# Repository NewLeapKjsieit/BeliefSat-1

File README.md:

# BeliefSat-1

BeliefSat-1 is a 2p-PocketQube standard student nano-satellite being developed by the undergraduate students of [**_K.J.Somaiya Institute of Engineering and Information Technology, Sion, Mumbai_** .](https://kjsieit.somaiya.edu/en) The satellite itself is a sub-part of team's proposal under [PS4-Orbital platform program](https://www.isro.gov.in/update/15-jun-2019/announcement-of-opportunity-ao-orbital-platform) of ISRO, wherein, team aims to demonstrate indegenously developed technologies for PocketQube standard nano-satellites. As a part of this demonstration, **BeliefSat** will be launched out of **SomaiyaPod** which is a Pocketqube standard deployer being indegenously developed at the institute. The unique construction technique, combination of COTS components for communication, on-board computer and power sub-systems , together constitute of **SomaiyaPQBus**, around which the satellite is being made, is also one of the technologies that the team wants to demonstrate and open-source to enable use by future missions.

## So what will BeliefSat do in space and what results it will give?

1. If it is successfully deployed out of the SomaiyaPod and completes startup procedure (it will be dead inside the Pod and will only get power after it is out of pod)and then sends a beacon; reliability of both deployer and the design of the satellite will be confirmed.
2. Every 1 minute, it will send a telemetry packet, which will have values from different COTS sensors. The team aims to project the activity of telemetry reception as a way of involving more students in to Software Defined Radio and RF in general.
3. It will have a functionality as of a amateur-radio digipeater. Which means if you hold a proper Amateur radio license then you can send a text message to the satellite and the satellite will repeat it (after delay of upto 10 seconds depending on other important processes running on-board). Making it a utility for Amateur radio community.
4. Not only it can digipeat a message it also has the functionality to repeat voice. For using this functionality you need a UHF transmitter and you can send a voice message to the satellite and the satellite will repeate it (after some delay depending on other important processes running on-board). It also will be a big utility for Amateur radio community.
5. If the satellite is able to operate for more than 3 months while responding to the commands and sending the health data at proper intervals, it will prove the reliablity of the unique design and set of COTS hardware used. Thus future mission could use flight proven hardwares for communication and power generation.

## What is it made of ?, What does it look like ?, What are its dimenssions and mass?

BeliefSat's structure is made by joining plates/PCBs(made out of FR4 material). This is a very novel approach in designing the structure of a satellite. Generally, satellites are made from Aluminium or its alloys, but using our novel approach we were able to design a very sturdy but cost effective sateliite. Although this technique is generally limited to nano-satellites. The PCBs that make the structure of our satellite have the solar panels and other components embedded in itself, so the complexity of assembly is minimized.

This is a concept render of our BeliefSat:

The dimension of the BeliefSat is in accordance with the PocketQube Standards. This standard includes a base plate on which the satellite is mounted and then it slides out of
the satellite deployer via rails. As per the standards, our BeliefSat is 2P ie, Base plate is 58mm x 128mm x 1.6mm (WxLxH), whereas the satellite is 58mm x 128mm x 50mm (WxLxH).
The estimated mass of BeliefSat is around 450 grams. The dimensions of our deployer (SomaiyaPod) are 145mm x 200mm x 95mm (WxLxH).

## How is it powered?

The satellite is powered by AltaDevices Single Juntion cells ([which unfortunately are out of buisness as of date of writing](https://pv-magazine-usa.com/2019/12/31/shutdown-continues-at-hanergy-owned-alta-devices-high-efficiency-pv-pioneer/)). Each of these cell produce 0.25W power when illumniated at intensity of 1000W/m^2. There are 4 such cells on long sides and 2 on shorter sides. So when illuminated, satellite may produce 0.5W watt/1watt/>1W depending on the orientation. The power remaining after being used is then stored in 2 parallely connected [2600mah Samsung 18650 batteries](https://robokits.co.in/batteries-chargers/samsung-premium-li-ion-battery/3.7v-samsung-li-ion-batteries/samsung-icr-18650-26j-2600mah-li-ion-cell-original?gclid=CjwKCAjwltH3BRB6EiwAhj0IUHaLyAB-D4SHw_PhNjM4cJyQy68a7cGyKCsCMS-I6JLJSGFChlp92BoC6-4QAvD_BwE). [SPV1040](https://www.st.com/en/power-management/spv1040.html) is used on every panel for maximum power point tracking and giving regulated voltage from the solar cells. The choice of SPV1040 was made based on flight history in [FossaSat-1](https://github.com/FOSSASystems/FOSSASAT-1). Now that AltaDevices cells won't be available in market, team will also be making one prototype with [SM141K06L by IXYS](https://www.digikey.com/product-detail/en/ixys/SM141K06L/SM141K06L-ND/9990462) and will be publishing test results for it too. 

## How does it communicate?

**_Transciever Specs_**
    **VHF**
-   **Name :** [DRA818V](http://www.dorji.com/products.php?Keyword=dra818v)
-   **Frequency Range :** 134~174 Mhz
-   **Channel Space :** 12.5/25 KHz
-   **TX Current :** 450/750 mA
-   **Temperature :** -20°C ~ +70°C
-   **Output Power :** +27/30 dbm
-   **Reciever Sensitivity :** -122 dbm (As per datasheet, observed sensititvity yet to be calculated)

    **UHF**
-   **Name :** [DRA818U](http://www.dorji.com/products.php?Keyword=dra818u)
-   **Frequency Range :** 400~470 Mhz
-   **Channel Space :** 25 KHz
-   **TX Current :** 450/750 mA
-   **Temperature :** -20°C ~ +70°C
-   **Output Power :** +27/30 dbm
-   **Reciever Sensitivity :** -122 dbm (As per datasheet, observed sensititvity yet to be calculated)
    _(UHF will only be used for voice repeater uplink)_
**_Antenna_**

Dipole made from measuring tape, which is in folded state during launch. Once in orbit, fishing cord which holds the antenna in folded position, is burnt by heating a resistor around which it is tied.

**_Link Budget_**

-   **Orbit Height :** 600 Km (proposed, may vary as per allocation by launch provider)
-   **Slant Range at 25 degree elevation :** 1213.4 Km (approximately)
-   **Free Space Path Loss at this distance for 145.825 MHz frequency :** 137.4 dbm
-   **Free Space Path Loss at this distance for 435.6 MHz frequency :** 146.9 dbm
-   **Received power neglecting mismatch,connector,atmospheric, pointing and polarization losses and receiving and transmitting antenna gains :** -118.2/-121.2 (op= 30/27dbm)
-   **Note :** A good directional antenna at receving groundstation (e.g. a 6 element yagi, plans for which will be released soon) can ensure the above mentioned losses are made up for and the signals can be received at even lower angles. However, to ensure best performance, circular polarized antennas copuled with a good LNA (e.g. [LNA4ALL](http://lna4all.blogspot.com/)) mounted over a Azimuth-Elevation antenna rotator (e.g. [Satnogs rotator](https://wiki.satnogs.org/SatNOGS_Rotator_v3)/[Sarcnet Rotator](https://www.sarcnet.org/rotator-mk2.html#RotatorMk2a)/[Yaesu G5500](https://www.yaesu.com/indexVS.cfm?cmd=DisplayProducts&ProdCatID=104&encProdID=79A89CEC477AA3B819EE02831F3FD5B8)/[WRAPS portable antenna rotator](https://ukamsat.files.wordpress.com/2013/12/wraps-mark-spencer-wa8sme-qst-jan-2014-copyright-arrl.pdf)) is recommended.

**_Data Rates in bps_**

-   **Telemetry Downlink :** 1200
-   **Digipeater Downlink :** 1200
-   **Command Uplink :** 1200
-   **Digipeater Uplink :** 1200

**_How the satellite complies with the requirment of turning off the transmitters when required ?_**
All the uplinks and downlinks occur on same frequency. Reciever is disabled while transmitting, to avoid interrupts to controller during the transmission, however, these transmissions last no more than 2 sec. This will ensure that one can relay a command during any pass. Also the transmitter is implemented to be active only when microcontroller is active, so if the main computer fails, the transmitter won't turn on. If the spacecraft computer is hung up for more than 8 sec, it resets along with the transciever. The automatic image capture mode is automatically turned off if battery voltage falls, thus adding extra layer of governance on the mode where long and continous transmission occurs. The satellite is designed to automatically turn off the microcontroller and thus the transciever in case of any thermal or short-circuit event. It is also protected against latchup situations caused by brown-outs or radiation flipping a bit, by the means of internal watchdog, which resets non-responsive or improperly finctioning controller after 8 sec. Whenever, required, satellites transmitters can be turned off until next command to turn those on by uplinking a command to do so. If the shut-down request comes when there is no pass over parent groundstation, the uplink packe format can be shared with a station which will have nearest pass.

## What are different packet types and packet formats ?

**_Telemetry Packet_**

**_APRS TELEMETRY FORMAT : The on-air packet telemetry format is as follows:_**

**T#sss,111,222,333,444,555,666,777,888,999,AAA,xxxxxxxx**
where,
-    sss : LSB of total number of system resets
-    111 : MSB of total number of system resets
-    222 : LSB of total number of resets induced by watch dog
-    333 : MSB of total number of resets induced by watch dog
-    444 : Temperature sensor 1 reading
-    555 : Temperature sensor 2 reading
-    666 : Gyro-sensor 1 reading
-    777 : Gyro-sensor 1 reading
-    888 : Gyro-sensor 1 reading
-    999 : Current reading
-    AAA : Voltage reading
-    xxxxxxxx : If the last two bits are 10 then digipeater is on and if they are 01 then voice repeater is on.

**References for converting Sensor data into readable format**

1. Temperature Sensor (DS18B20) :- [Datasheet](https://pdf1.alldatasheet.com/datasheet-pdf/view/58557/DALLAS/DS18B20.html)

2. Gyro Sensor (MPU-6050) :- [Datasheet](https://invensense.tdk.com/wp-content/uploads/2015/02/MPU-6000-Datasheet1.pdf)

3. Current/Power Sensor (INA219) :- [Datasheet](https://www.ti.com/lit/ds/symlink/ina219.pdf?ts=1593455980944&ref_url=https%253A%252F%252Fwww.google.com%252F)

**Reference for transreceivers**

1. DRA818V :- [Datasheet](http://www.dorji.com/docs/data/DRA818V.pdf)

2. DRA818U :- [Datasheet](http://www.dorji.com/docs/data/DRA818U.pdf)

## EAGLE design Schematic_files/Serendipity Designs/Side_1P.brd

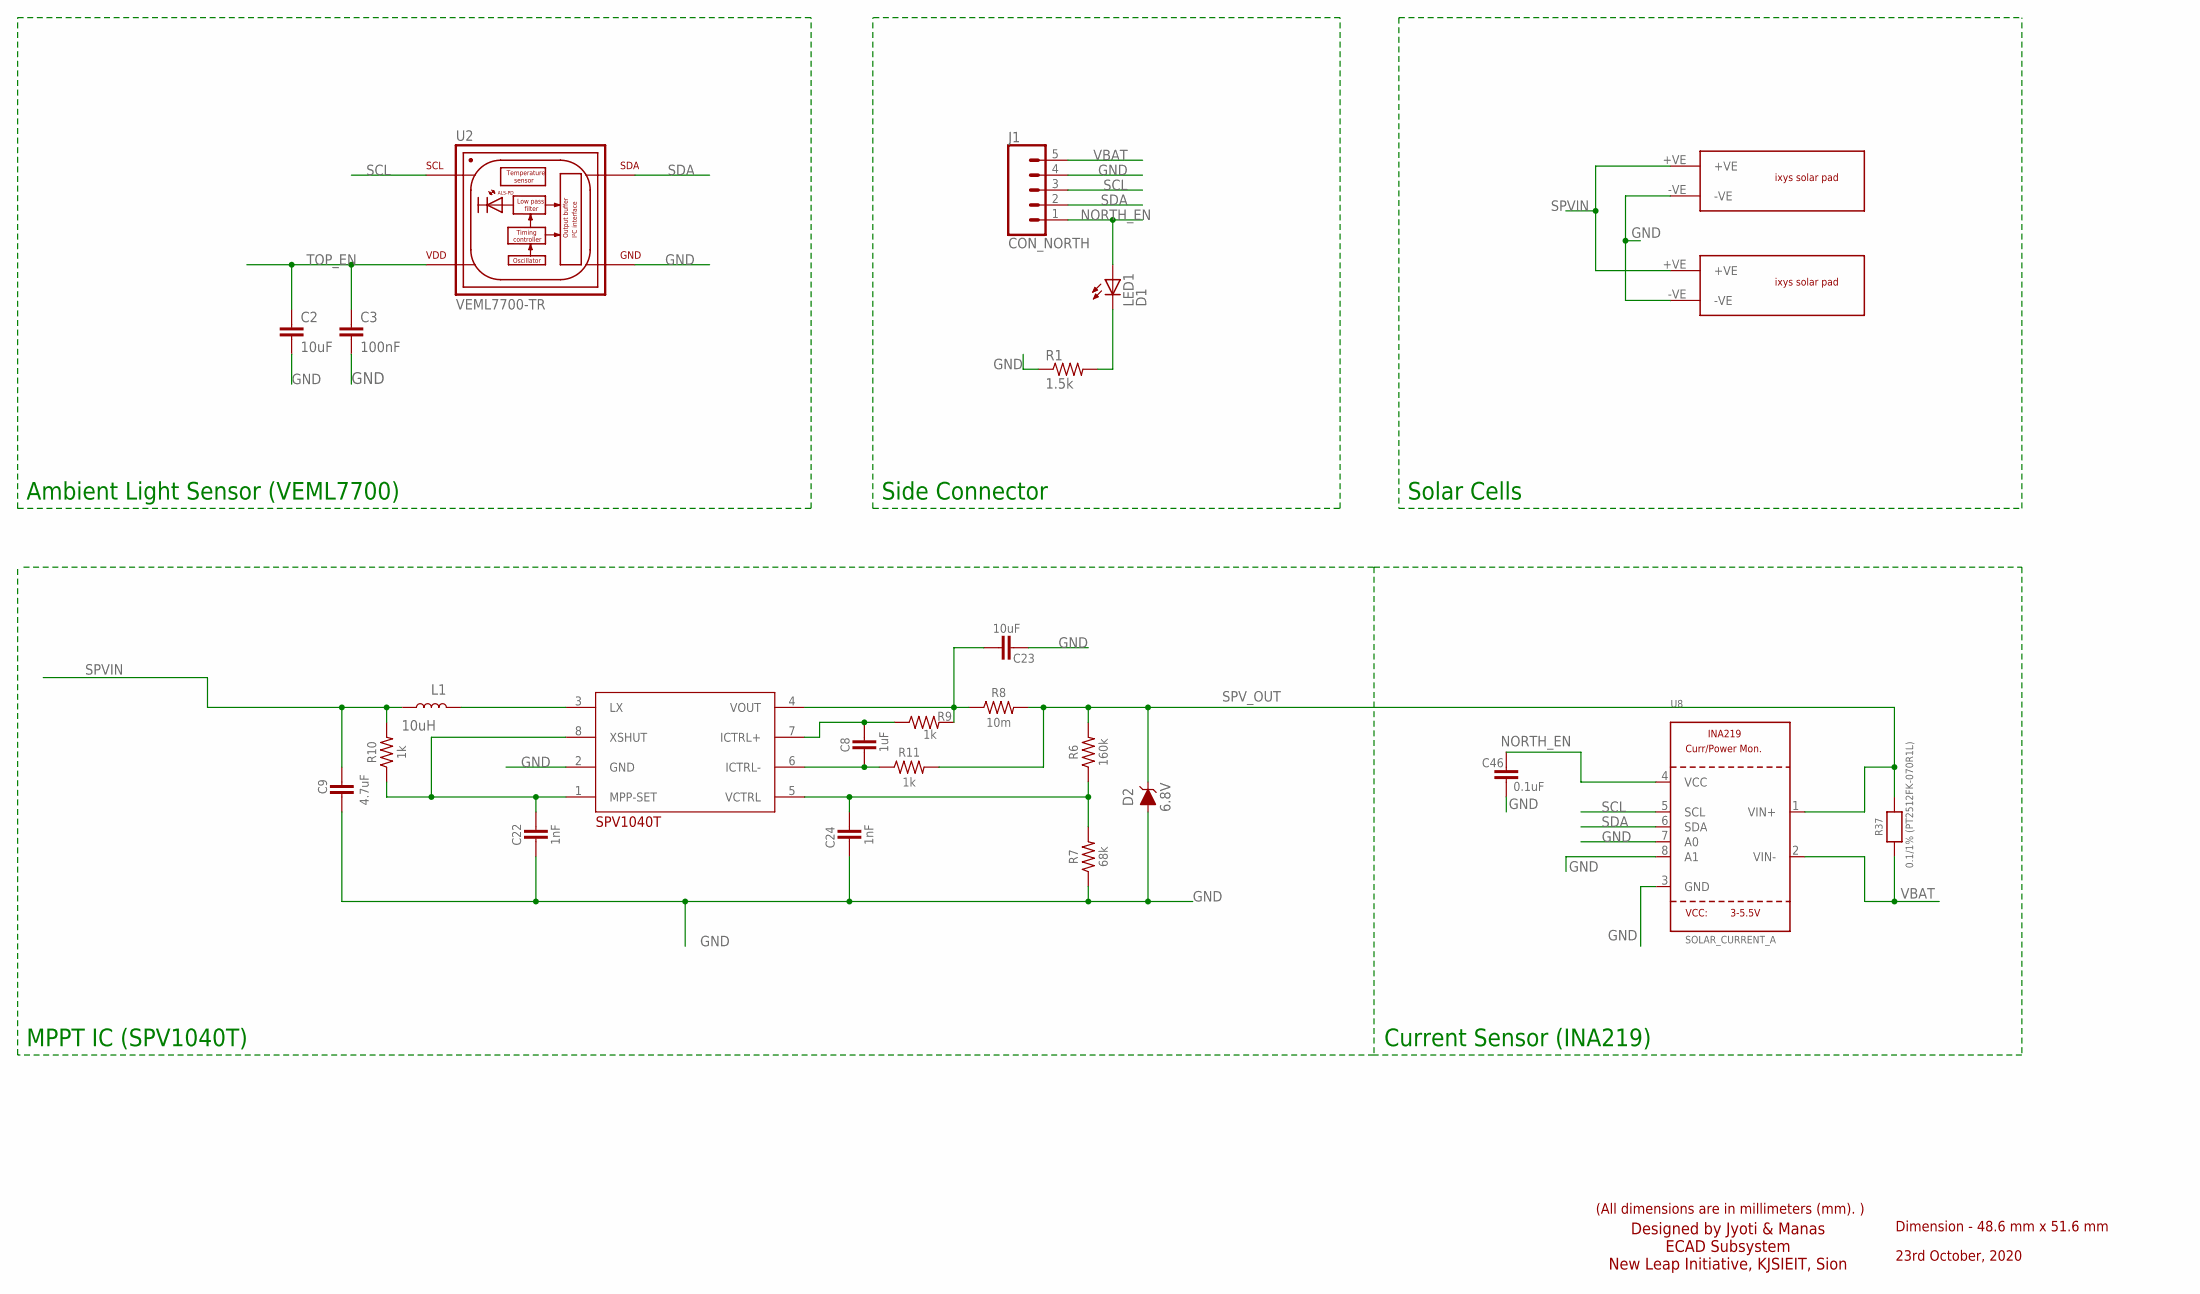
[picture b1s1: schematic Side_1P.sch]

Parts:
C2, C23: 10uF; 0603
C3: 100nF; 0603
C8: 1uF; 0603
C9: 4.7uF; 0603
C22, C24: 1nF; 0603
C46: 0.1uF; 0603
D2: 6.8V; SOD-323
J1: CON_NORTH; 1X05_1.27MM
L1: 10uH; 0603
LED1: D1; CHIP-LED0603
R1: 1.5k; R0603
R6: 160k; RES_0603
R7: 68k; RES_0603
R8: 10m; RES_0603
R9, R10, R11: 1k; RES_0603
R37: 0.1/1% (PT2512FK-070R1L); 2512
SPV_A: SPV1040T_; SOP65P640X120-8N
U2: VEML7700-TR; XDCR_VEML7700-TR
U8: SOLAR_CURRENT_A; SOT23-8
U$1, U$2: IXYS

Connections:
GND: C2.2, C3.2, C9.2, C22.2, C23.2, C24.2, C46.2, D2.A, J1.4, R1.1, R7.1, SPV_A.2 (GND), U2.3 (GND), U8.3 (GND), U8.7 (A0), U8.8 (A1), U$1.-VE, U$2.-VE
unnamed: LED1.C, R1.2
unnamed: L1.2, SPV_A.3 (LX)
unnamed: C22.1, R10.1, SPV_A.1 (MPP-SET), SPV_A.8 (XSHUT)
unnamed: C24.1, R6.1, R7.2, SPV_A.5 (VCTRL)
unnamed: C8.2, R11.1, SPV_A.6 (ICTRL-)
unnamed: C8.1, R9.1, SPV_A.7 (ICTRL+)
unnamed: C23.1, R8.1, R9.2, SPV_A.4 (VOUT)
NORTH_EN: C46.1, J1.1, LED1.A, U8.4 (VCC)
SCL: J1.3, U2.1 (SCL), U8.5 (SCL)
SDA: J1.2, U2.4 (SDA), U8.6 (SDA)
SPVIN: C9.1, L1.1, R10.2, U$1.+VE, U$2.+VE
SPV_OUT: D2.C, R6.2, R8.2, R11.2, R37.2, U8.1 (VIN+)
TOP_EN: C2.1, C3.1, U2.2 (VDD)
VBAT: J1.5, R37.1, U8.2 (VIN-)

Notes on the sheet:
Ambient Light Sensor (VEML7700)
Side Connector
Solar Cells
MPPT IC (SPV1040T)
Current Sensor (INA219)
Dimension - 48.6 mm x 51.6 mm
23rd October, 2020
(All dimensions are in millimeters (mm). )
Designed by Jyoti & Manas ECAD Subsystem New Leap Initiative, KJSIEIT, Sion

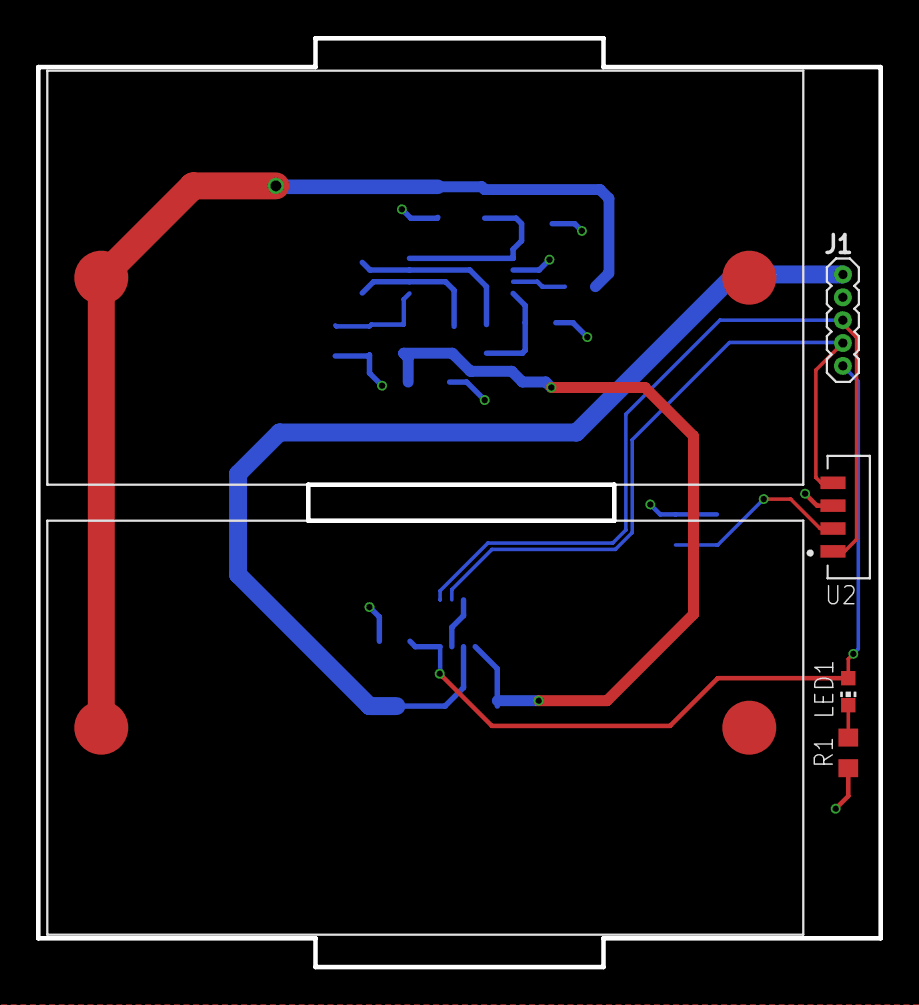
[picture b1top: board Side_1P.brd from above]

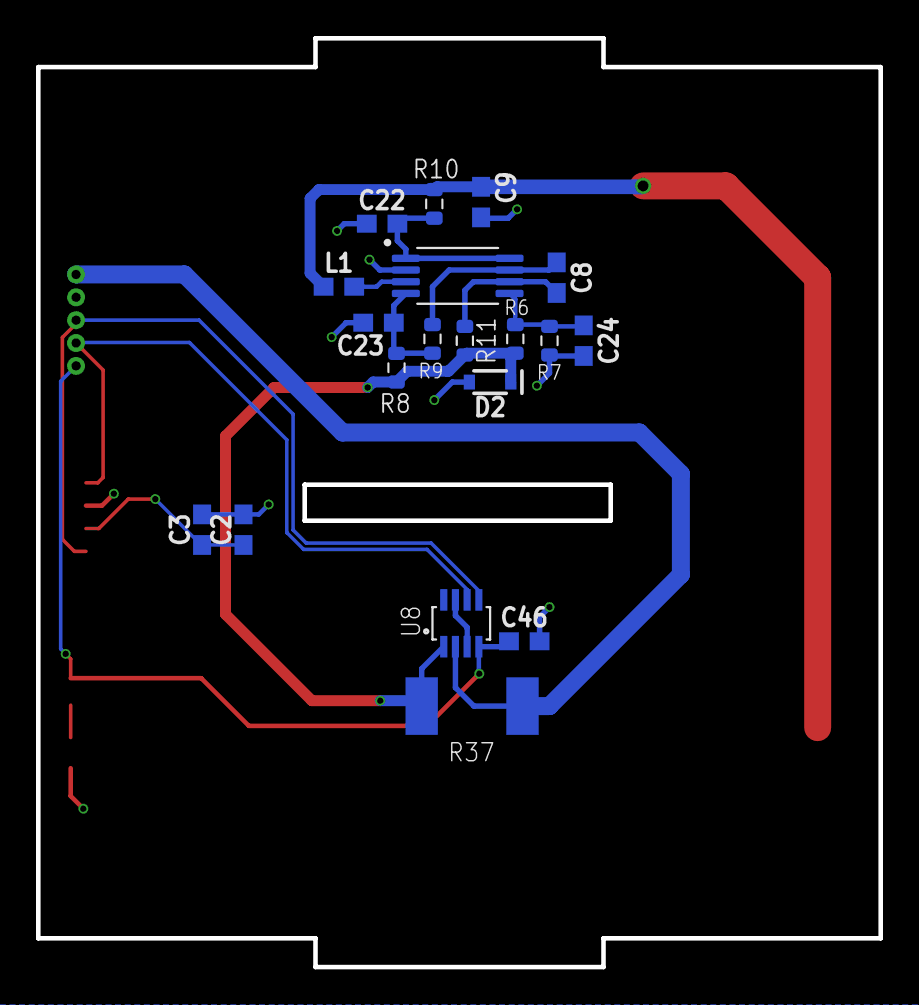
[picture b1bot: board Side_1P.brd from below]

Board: 2 copper layers, 46.8 x 51.6 mm, 25 parts (19 on the bottom side), 15 nets.

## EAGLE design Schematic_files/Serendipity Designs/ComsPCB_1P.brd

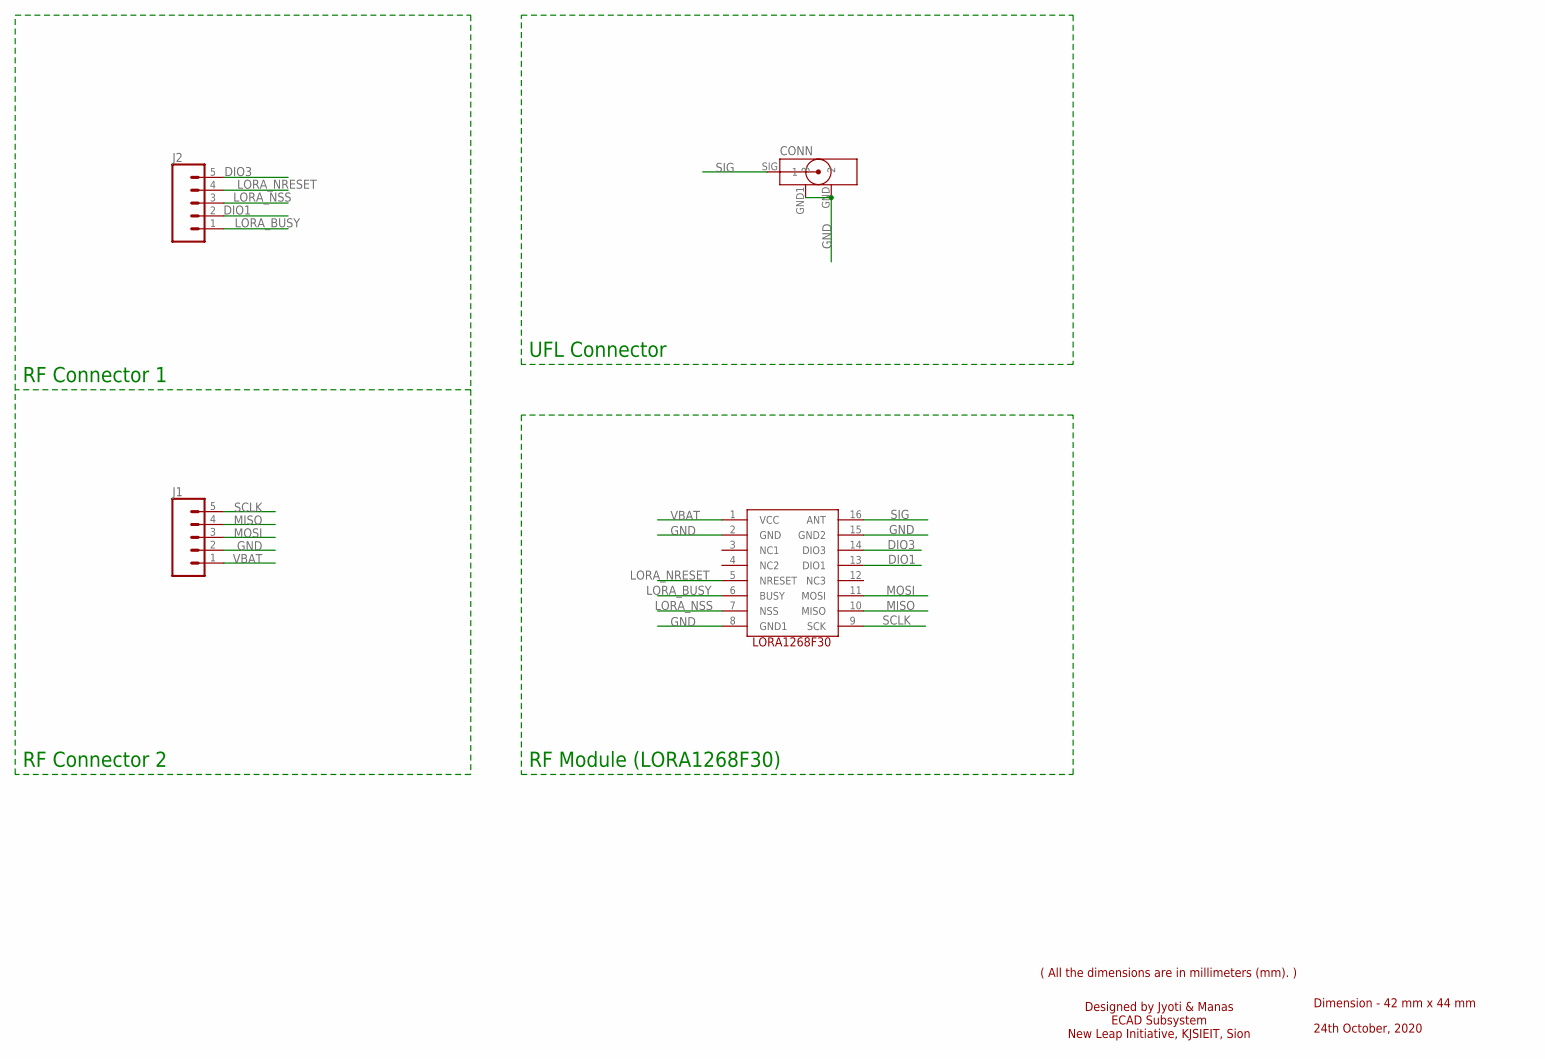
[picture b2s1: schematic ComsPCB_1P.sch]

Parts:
CONN: U.FL-R-SMT(10)
J1, J2: CONN_051.27MM; 1X05_1.27MM
U$1: U1; LORA1268F30

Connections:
DIO1: J2.2, U$1.13 (DIO1)
DIO3: J2.5, U$1.14 (DIO3)
GND: CONN.GND (2), CONN.GND1 (3), J1.2, U$1.2 (GND), U$1.8 (GND1), U$1.15 (GND2)
LORA_BUSY: J2.1, U$1.6 (BUSY)
LORA_NRESET: J2.4, U$1.5 (NRESET)
LORA_NSS: J2.3, U$1.7 (NSS)
MISO: J1.4, U$1.10 (MISO)
MOSI: J1.3, U$1.11 (MOSI)
SCLK: J1.5, U$1.9 (SCK)
SIG: CONN.SIG (1), U$1.16 (ANT)
VBAT: J1.1, U$1.1 (VCC)

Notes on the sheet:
Dimension - 42 mm x 44 mm
24th October, 2020
( All the dimensions are in millimeters (mm). )
Designed by Jyoti & Manas ECAD Subsystem New Leap Initiative, KJSIEIT, Sion
RF Module (LORA1268F30)
UFL Connector
RF Connector 1
RF Connector 2

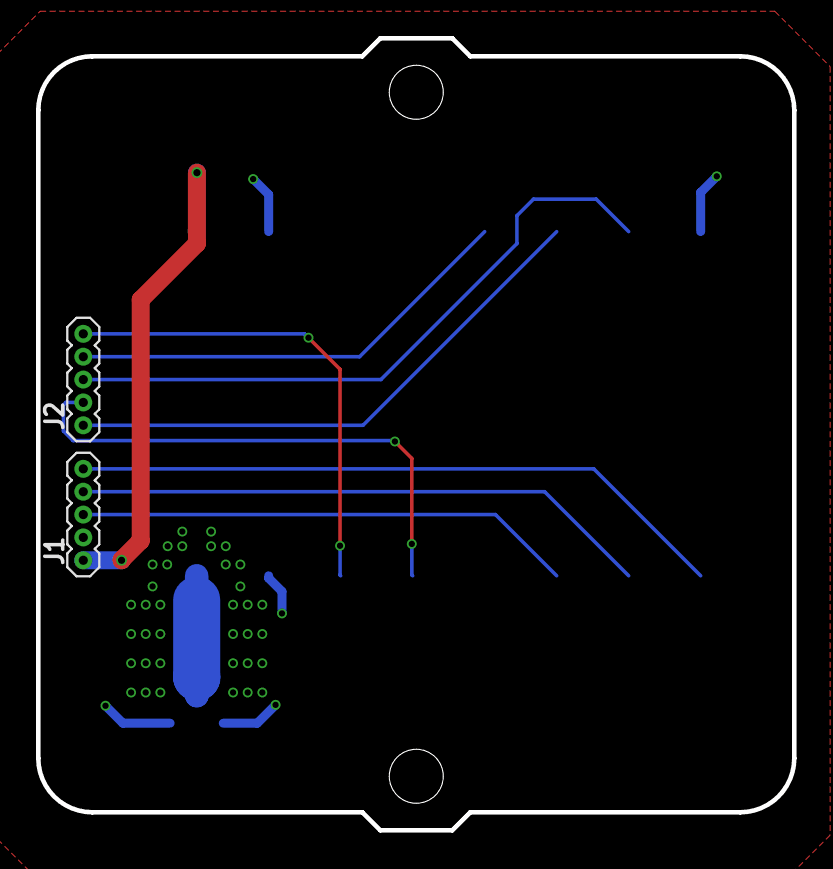
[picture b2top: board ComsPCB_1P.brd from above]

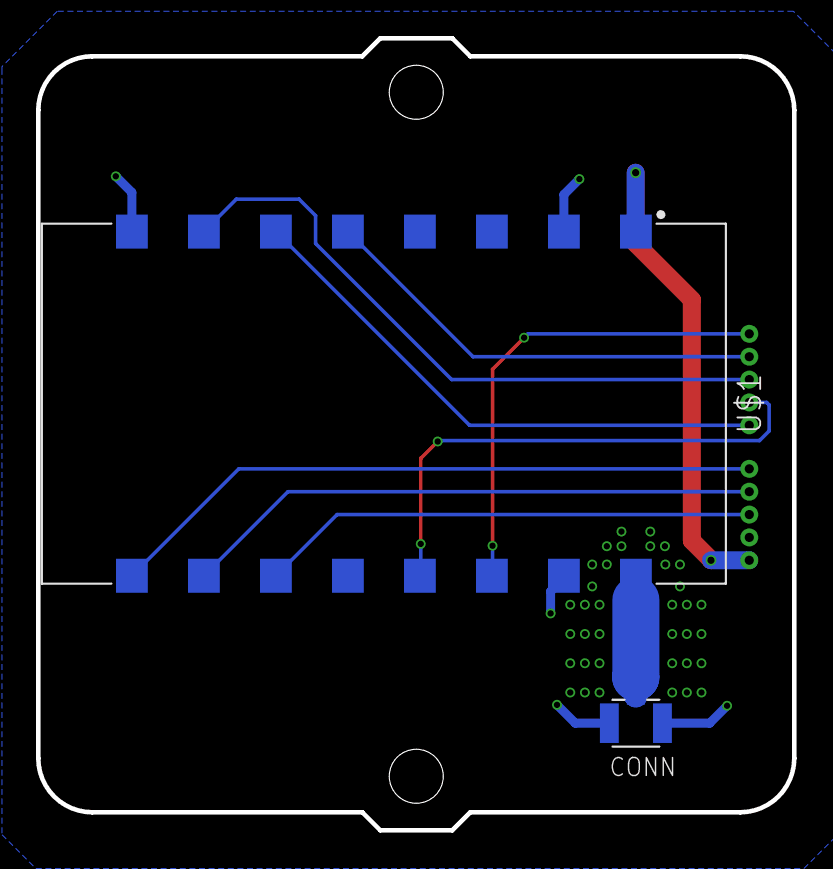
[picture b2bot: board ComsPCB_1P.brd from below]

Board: 2 copper layers, 42.0 x 44.0 mm, 4 parts (2 on the bottom side), 11 nets.

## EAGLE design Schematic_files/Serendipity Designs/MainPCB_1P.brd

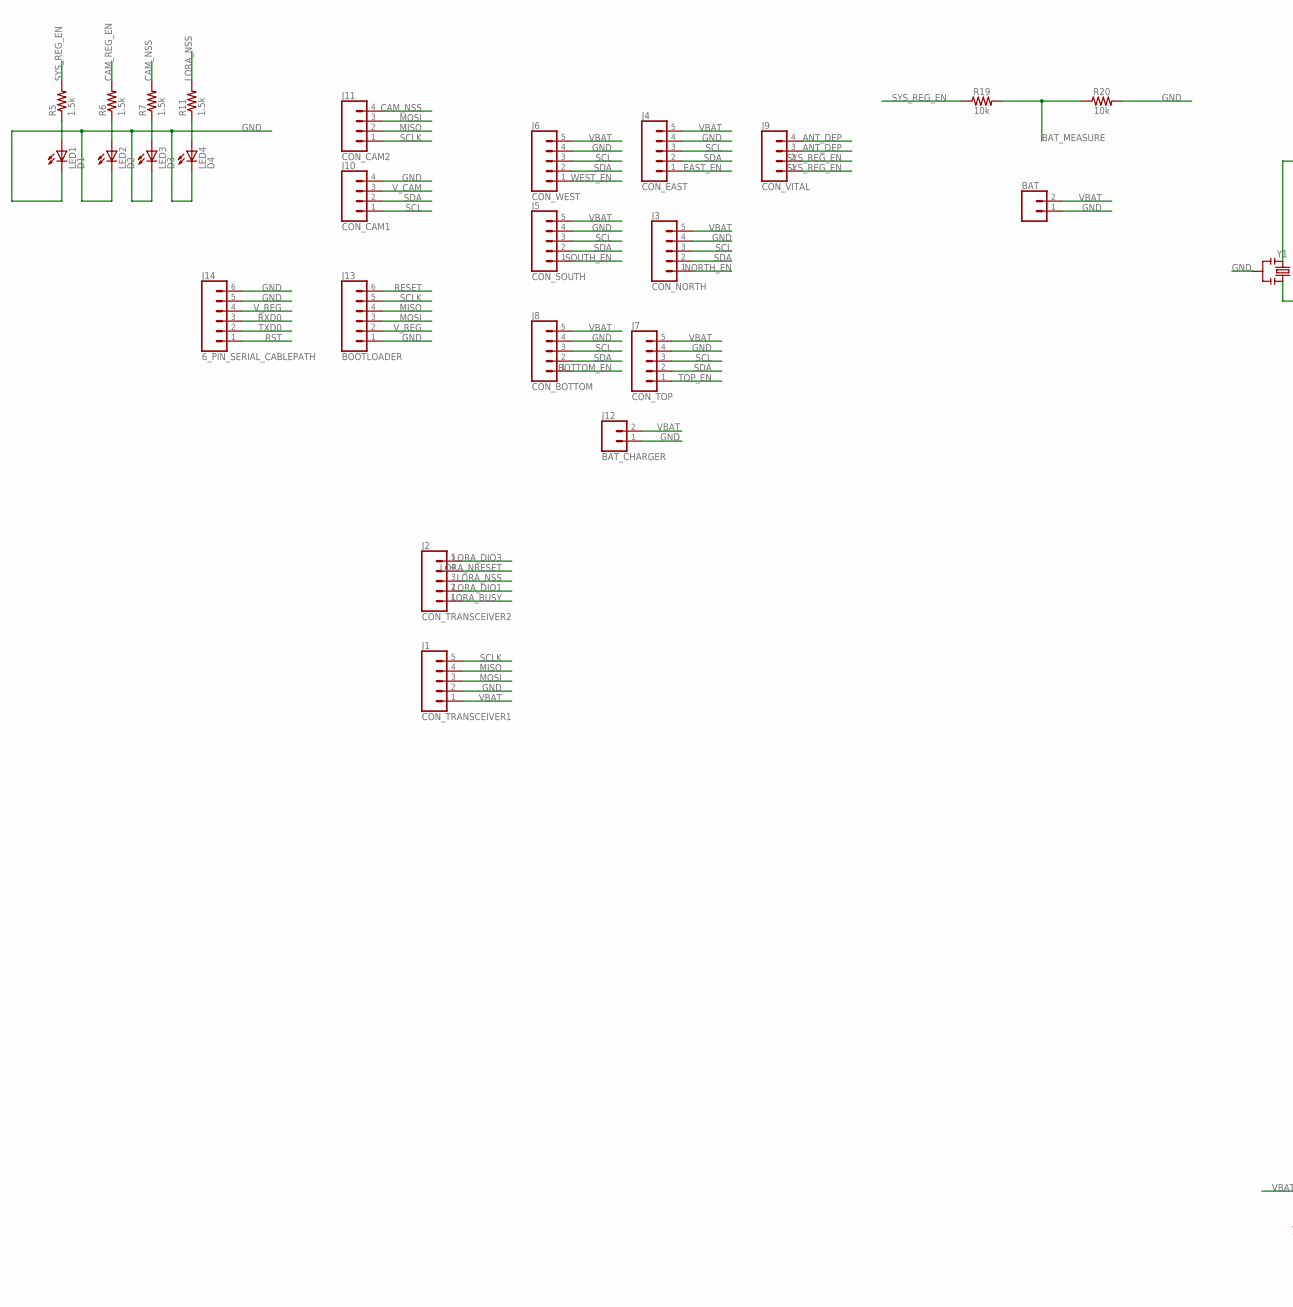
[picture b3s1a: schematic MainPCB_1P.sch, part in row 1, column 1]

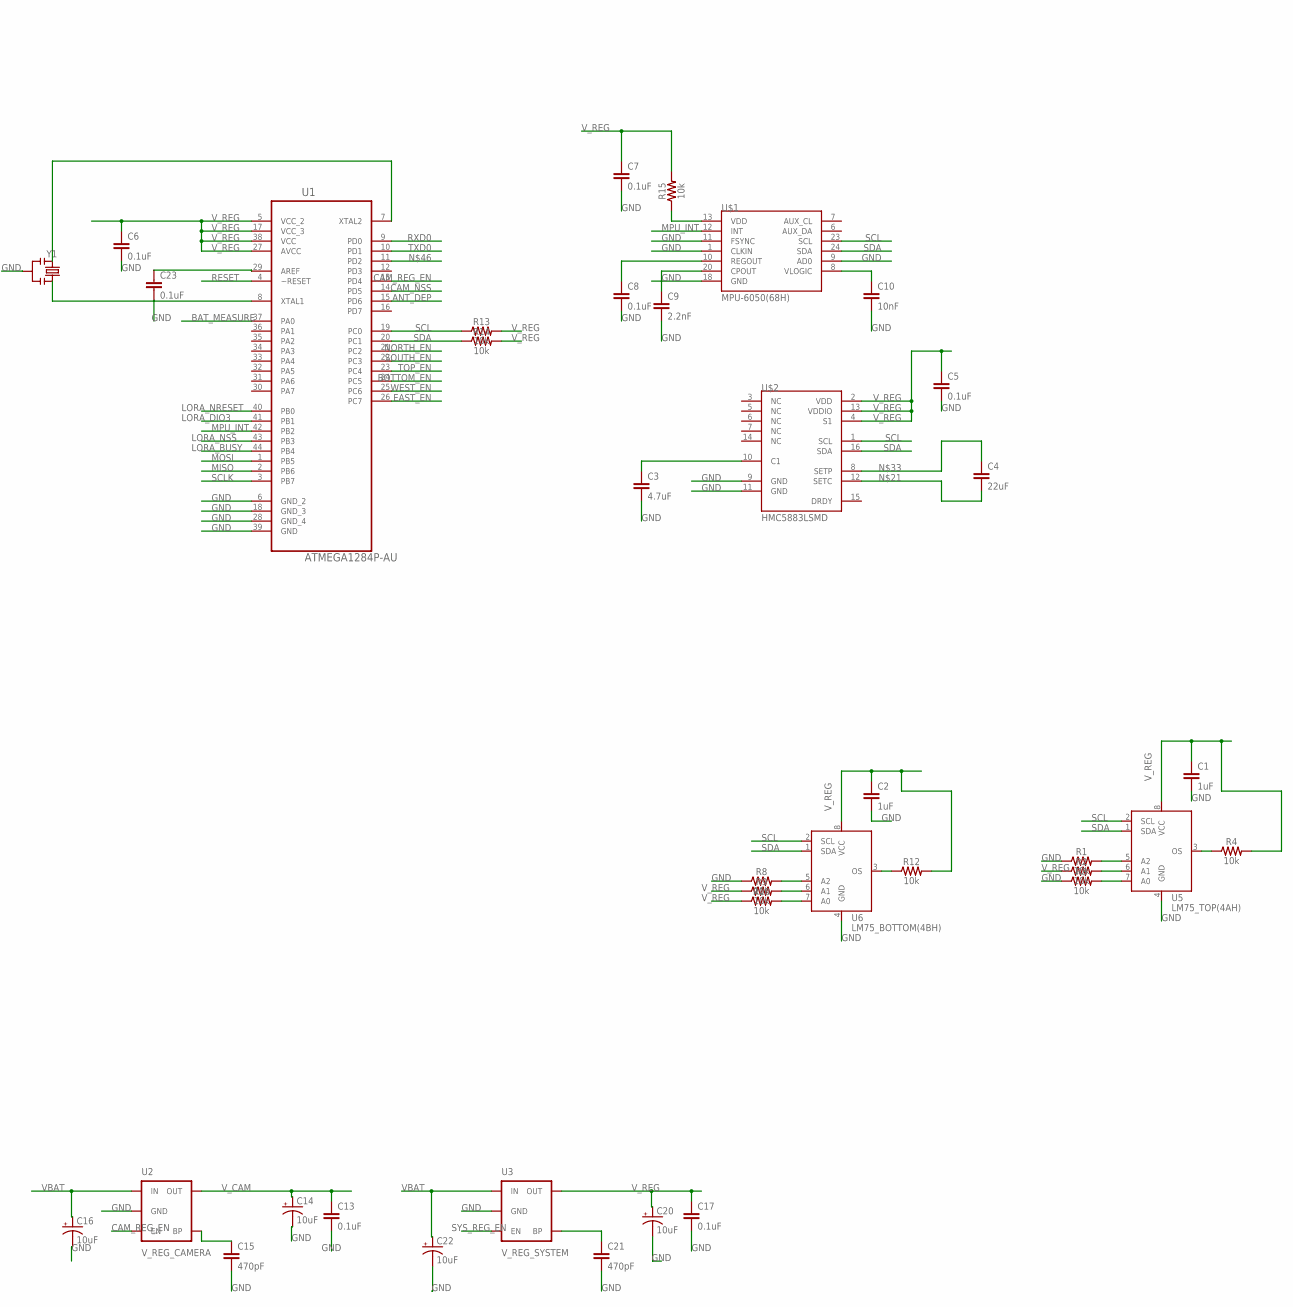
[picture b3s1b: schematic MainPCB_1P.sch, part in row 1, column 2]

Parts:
BAT: CONN_02; 1X02
C1, C2: 1uF; 0603
C3: 4.7uF; 0603
C4: 22uF; 0603
C5, C6, C7, C8, C13, C17: 0.1uF; 0603
C9: 2.2nF; 0603
C10: 10nF; 0603
C14, C16, C20, C22: 10uF; 0603-POLAR
C15, C21: 470pF; 0603
C23: 0.1uF; 0603-CAP
J1: CON_TRANSCEIVER1; 1X05_1.27MM
J2: CON_TRANSCEIVER2; 1X05_1.27MM
J3: CON_NORTH; 1X05_1.27MM
J4: CON_EAST; 1X05_1.27MM
J5: CON_SOUTH; 1X05_1.27MM
J6: CON_WEST; 1X05_1.27MM
J7: CON_TOP; 1X05_1.27MM
J8: CON_BOTTOM; 1X05_1.27MM
J9: CON_VITAL; 1X04_1.27MM
J10: CON_CAM1; 1X04_1.27MM
J11: CON_CAM2; 1X04_1.27MM
J12: BAT_CHARGER; 1X02_NO_SILK
J13: BOOTLOADER; 1X06_1.27MM
J14: 6_PIN_SERIAL_CABLEPATH; 1X06_1.27MM
LED1: D1; CHIP-LED0603
LED2: D2; CHIP-LED0603
LED3: D3; CHIP-LED0603
LED4: D4; CHIP-LED0603
R1, R2, R3, R4, R8, R9, R10, R12, R13, R14, R15, R19, R20: 10k; 0603
R5, R6, R7, R11: 1.5k; R0603
U1: ATMEGA1284P-AU; QFP80P1200X1200X120-44N
U2: V_REG_CAMERA; SOT23-5
U3: V_REG_SYSTEM; SOT23-5
U5: LM75_TOP(4AH); SOT505-1
U6: LM75_BOTTOM(4BH); SOT505-1
U$1: MPU-6050(68H); QFN-24-4MM2
U$2: HMC5883LSMD; 16LPCC
Y1: RESONATORSMD; RESONATOR-SMD

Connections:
ANT_DEP: J9.3, J9.4, U1.15 (PD6)
BAT_MEASURE: R19.2, R20.1, U1.37 (PA0)
BOTTOM_EN: J8.1, U1.24 (PC5)
CAM_NSS: J11.4, R7.2, U1.14 (PD5)
CAM_REG_EN: R6.2, U1.13 (PD4), U2.3 (EN)
EAST_EN: J4.1, U1.26 (PC7)
GND: BAT.1, C1.2, C2.2, C3.2, C5.2, C6.2, C7.2, C8.2, C9.2, C10.2, C13.2, C14.-, C15.2, C16.-, C17.2, C20.-, C21.2, C22.-, C23.2, J1.2, J3.4, J4.4, J5.4, J6.4, J7.4, J8.4, J10.4, J12.1, J13.1, J14.5, J14.6, LED1.C, LED2.C, LED3.C, LED4.C, R1.1, R3.1, R8.1, R20.2, U1.6 (GND_2), U1.18 (GND_3), U1.28 (GND_4), U1.39 (GND), U2.2 (GND), U3.2 (GND), U5.4 (GND), U6.4 (GND), U$1.1 (CLKIN), U$1.9 (AD0), U$1.11 (FSYNC), U$1.18 (GND), U$2.9 (GND), U$2.11 (GND), Y1.2
LORA_BUSY: J2.1, U1.44 (PB4)
LORA_DIO1: J2.2
LORA_DIO3: J2.5, U1.41 (PB1)
LORA_NRESET: J2.4, U1.40 (PB0)
LORA_NSS: J2.3, R11.2, U1.43 (PB3)
MISO: J1.4, J11.2, J13.4, U1.2 (PB6)
MOSI: J1.3, J11.3, J13.3, U1.1 (PB5)
MPU_INT: U1.42 (PB2), U$1.12 (INT)
unnamed: C23.1, U1.29 (AREF)
unnamed: R1.2, U5.5 (A2)
unnamed: U1.7 (XTAL2), Y1.1
unnamed: U1.8 (XTAL1), Y1.3
unnamed: C3.1, U$2.10 (C1)
unnamed: C9.1, U$1.20 (CPOUT)
unnamed: C8.1, U$1.10 (REGOUT)
unnamed: R15.1, U$1.13 (VDD)
unnamed: R2.2, U5.6 (A1)
unnamed: C10.1, U$1.8 (VLOGIC)
unnamed: R8.2, U6.5 (A2)
unnamed: R9.2, U6.6 (A1)
unnamed: R10.2, U6.7 (A0)
unnamed: R3.2, U5.7 (A0)
unnamed: C4.2, U$2.12 (SETC)
unnamed: R4.1, U5.3 (OS)
unnamed: C21.1, U3.4 (BP)
unnamed: LED1.A, R5.1
unnamed: LED2.A, R6.1
unnamed: C15.1, U2.4 (BP)
unnamed: LED3.A, R7.1
unnamed: LED4.A, R11.1
unnamed: C4.1, U$2.8 (SETP)
unnamed: R12.1, U6.3 (OS)
NORTH_EN: J3.1, U1.21 (PC2)
RESET: J13.6, U1.4 (~RESET)
RST: J14.1
RXD0: J14.3, U1.9 (PD0)
SCL: J3.3, J4.3, J5.3, J6.3, J7.3, J8.3, J10.1, R13.1, U1.19 (PC0), U5.2 (SCL), U6.2 (SCL), U$1.23 (SCL), U$2.1 (SCL)
SCLK: J1.5, J11.1, J13.5, U1.3 (PB7)
SDA: J3.2, J4.2, J5.2, J6.2, J7.2, J8.2, J10.2, R14.1, U1.20 (PC1), U5.1 (SDA), U6.1 (SDA), U$1.24 (SDA), U$2.16 (SDA)
SOUTH_EN: J5.1, U1.22 (PC3)
SYS_REG_EN: J9.1, J9.2, R5.2, R19.1, U3.3 (EN)
TOP_EN: J7.1, U1.23 (PC4)
TXD0: J14.2, U1.10 (PD1)
VBAT: BAT.2, C16.+, C22.+, J1.1, J3.5, J4.5, J5.5, J6.5, J7.5, J8.5, J12.2, U2.1 (IN), U3.1 (IN)
V_CAM: C13.1, C14.+, J10.3, U2.5 (OUT)
V_REG: C1.1, C2.1, C5.1, C6.1, C7.1, C17.1, C20.+, J13.2, J14.4, R2.1, R4.2, R9.1, R10.1, R12.2, R13.2, R14.2, R15.2, U1.5 (VCC_2), U1.17 (VCC_3), U1.27 (AVCC), U1.38 (VCC), U3.5 (OUT), U5.8 (VCC), U6.8 (VCC), U$2.2 (VDD), U$2.4 (S1), U$2.13 (VDDIO)
WEST_EN: J6.1, U1.25 (PC6)

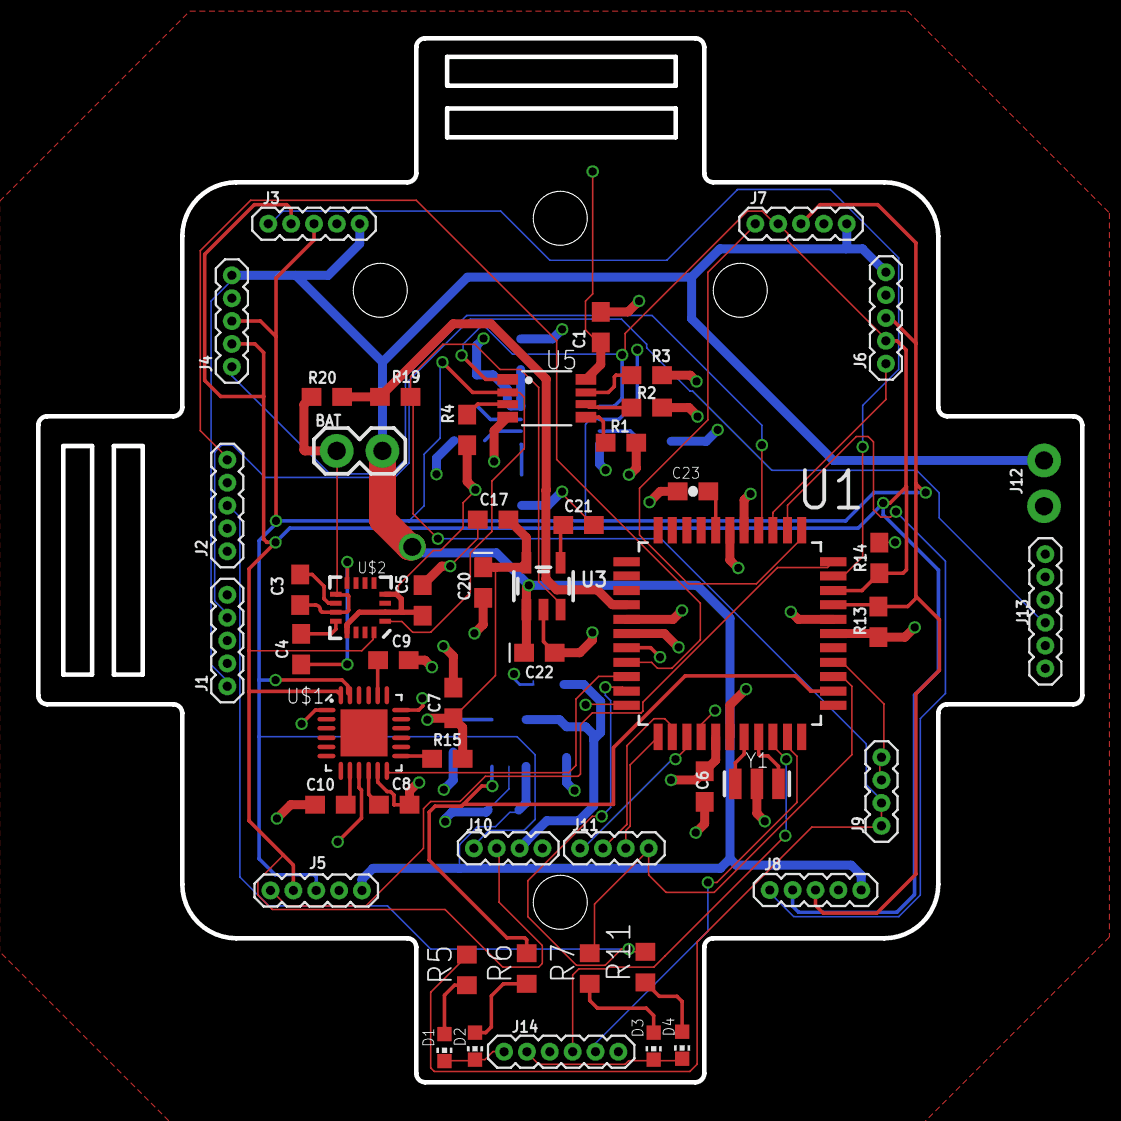
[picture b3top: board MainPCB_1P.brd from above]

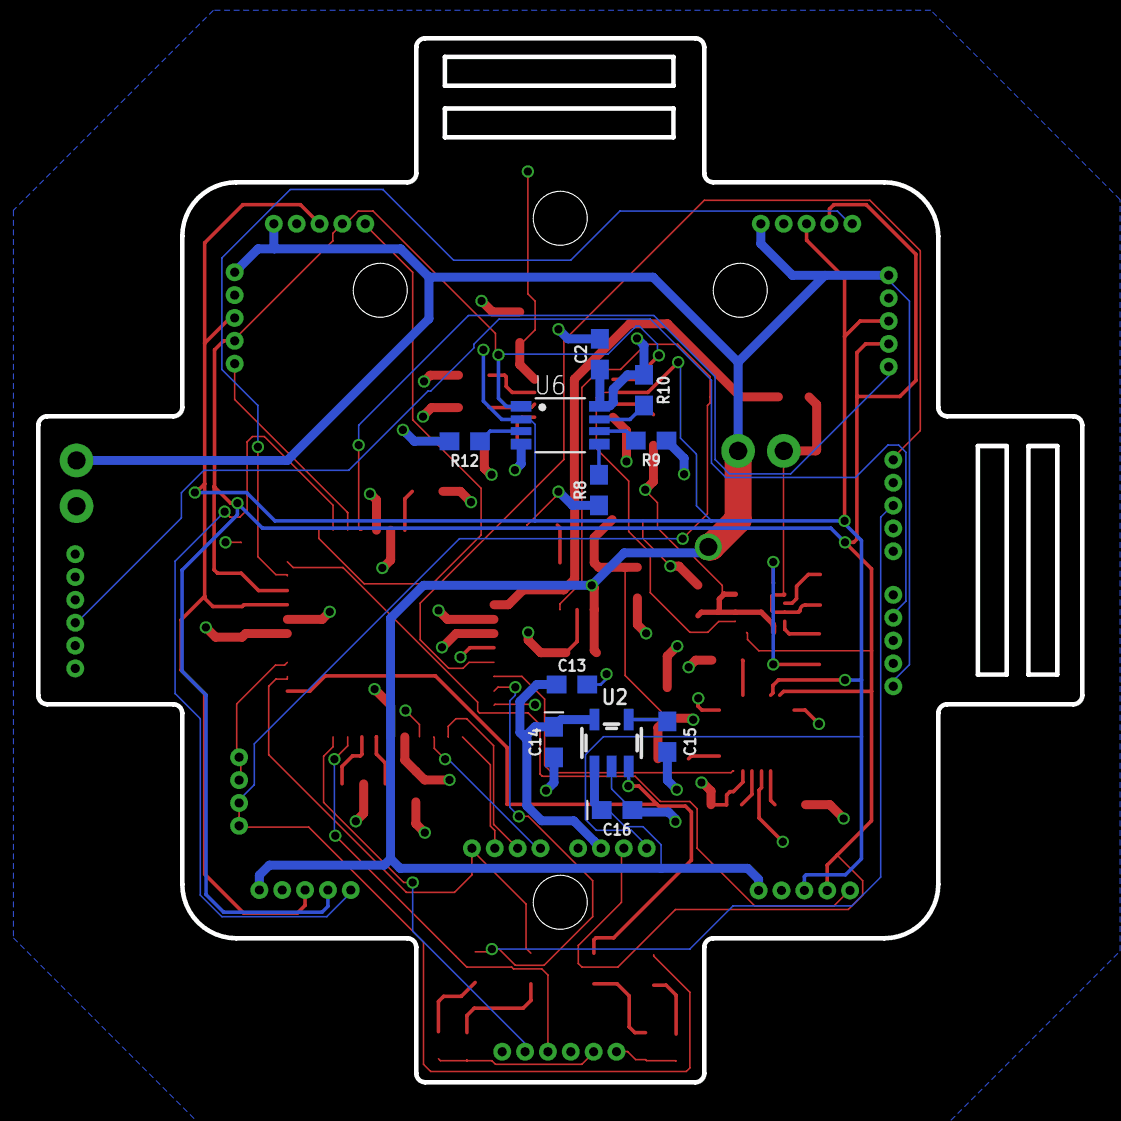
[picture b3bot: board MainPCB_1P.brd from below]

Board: 4 copper layers, 58.0 x 58.0 mm, 63 parts (11 on the bottom side), 52 nets.

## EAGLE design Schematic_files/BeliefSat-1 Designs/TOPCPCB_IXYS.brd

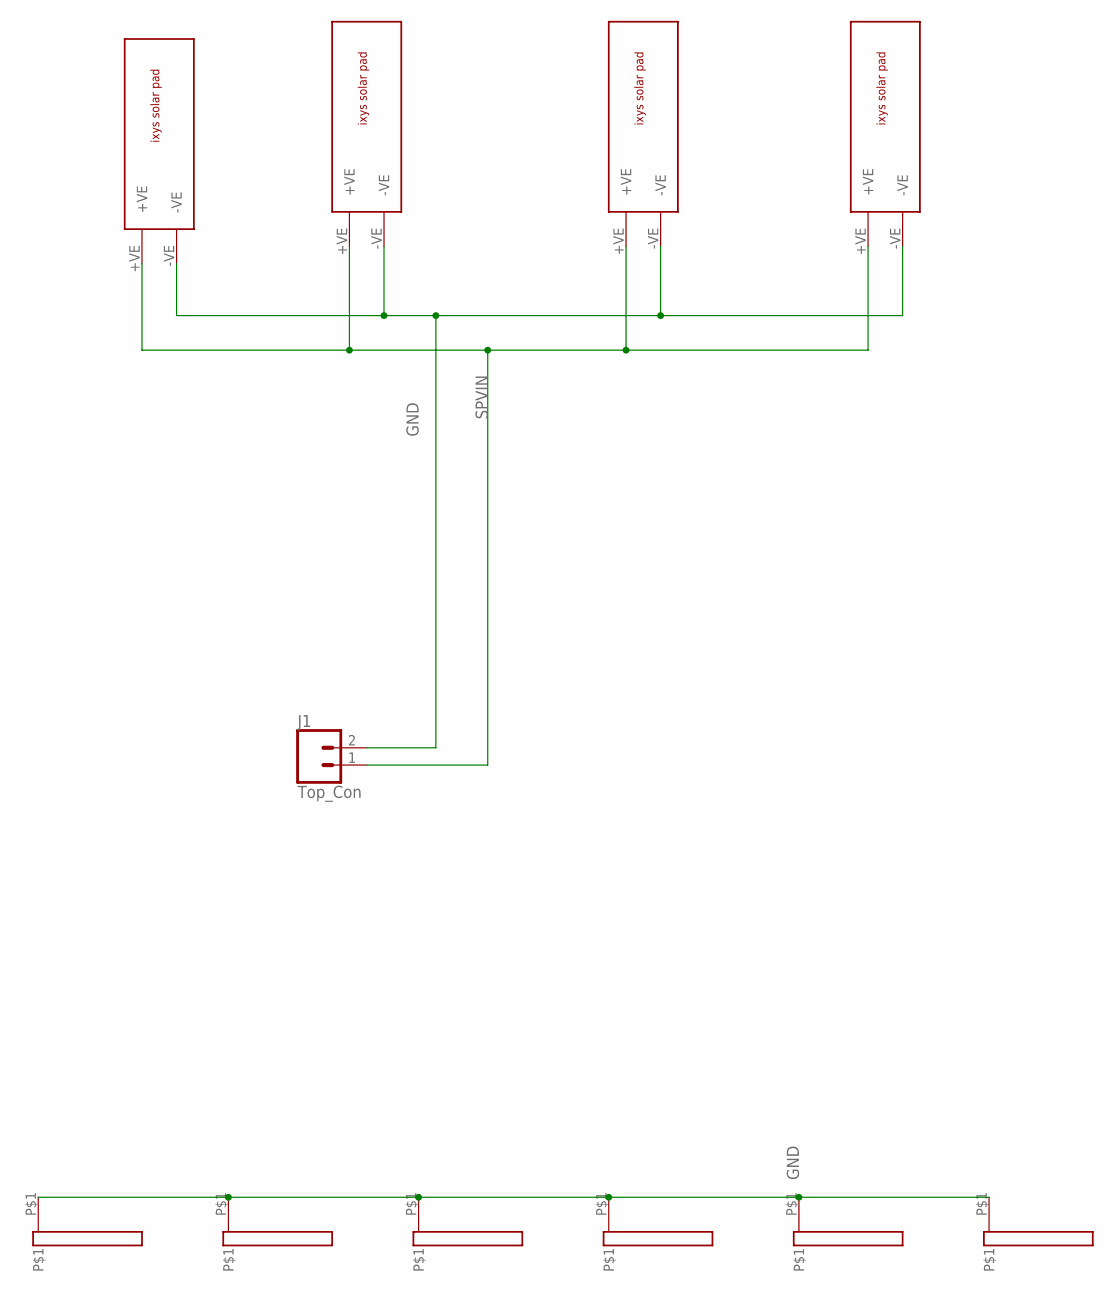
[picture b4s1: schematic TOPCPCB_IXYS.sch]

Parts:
J1: Top_Con; 1X02
LEFTSOLD: 16X2
U$1, U$4, U$5, U$7, U$9: 16X2
U$2, U$3, U$6, U$8: IXYS

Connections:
GND: J1.2, LEFTSOLD.P$1, U$1.P$1, U$2.-VE, U$3.-VE, U$4.P$1, U$5.P$1, U$6.-VE, U$7.P$1, U$8.-VE, U$9.P$1
SPVIN: J1.1, U$2.+VE, U$3.+VE, U$6.+VE, U$8.+VE

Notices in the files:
parts and their libraries:
SparkFun-Connectors: Licensing: Creative Commons ShareAlike 4.0 International - https://creativecommons.org/licenses/by-sa/4.0
microbuilder: This work is placed in the public domain, and may be freely used for commercial and non-commercial work with the following conditions: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
